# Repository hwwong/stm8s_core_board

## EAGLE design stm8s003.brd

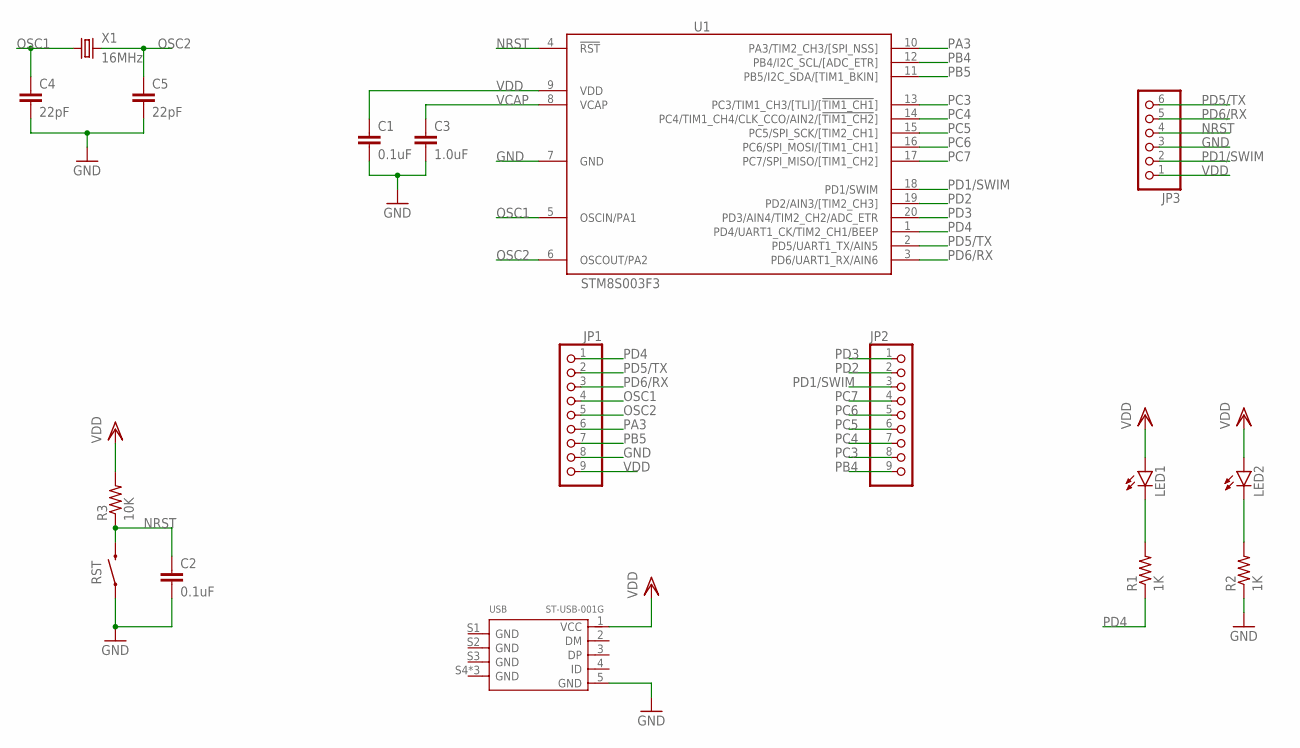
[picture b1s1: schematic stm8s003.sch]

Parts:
C1, C2: 0.1uF; 0603-CAP
C3: 1.0uF; 0603-CAP
C4, C5: 22pF; 0603-CAP
JP1, JP2: PINHD-1X9; 1X09-BIG
JP3: PINHD-1X6; 1X06
LED1, LED2: LED0603; LED-0603
R1, R2: 1K; 0603-RES
R3: 10K; 0603-RES
RST: SWITCH-MOMENTARY-2SMD-1101NE; TACTILE-SWITCH-1101NE
U1: STM8S003F3; TSSOP20
USB: ST-USB-001G; MICRO-USB5+4P-SMD-0.65-B
X1: 16MHz; HC49US

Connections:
GND: C1.2, C2.2, C3.2, C4.2, C5.2, JP1.8, JP3.3, R2.1, RST.1, U1.7 (GND), USB.5 (GND)
unnamed: LED1.C, R1.2
unnamed: LED2.C, R2.2
NRST: C2.1, JP3.4, R3.1, RST.2, U1.4 (!RST)
OSC1: C4.1, JP1.4, U1.5 (OSCIN/PA1), X1.1
OSC2: C5.1, JP1.5, U1.6 (OSCOUT/PA2), X1.2
PA3: JP1.6, U1.10 (PA3/TIM2_CH3/[SPI_NSS])
PB4: JP2.9, U1.12 (PB4/I2C_SCL/[ADC_ETR])
PB5: JP1.7, U1.11 (PB5/I2C_SDA/[TIM1_BKIN])
PC3: JP2.8, U1.13 (PC3/TIM1_CH3/[TLI]/[!TIM1_CH1!])
PC4: JP2.7, U1.14 (PC4/TIM1_CH4/CLK_CCO/AIN2/[!TIM1_CH2!])
PC5: JP2.6, U1.15 (PC5/SPI_SCK/[TIM2_CH1])
PC6: JP2.5, U1.16 (PC6/SPI_MOSI/[TIM1_CH1])
PC7: JP2.4, U1.17 (PC7/SPI_MISO/[TIM1_CH2])
PD1/SWIM: JP2.3, JP3.2, U1.18 (PD1/SWIM)
PD2: JP2.2, U1.19 (PD2/AIN3/[TIM2_CH3])
PD3: JP2.1, U1.20 (PD3/AIN4/TIM2_CH2/ADC_ETR)
PD4: JP1.1, R1.1, U1.1 (PD4/UART1_CK/TIM2_CH1/BEEP)
PD5/TX: JP1.2, JP3.6, U1.2 (PD5/UART1_TX/AIN5)
PD6/RX: JP1.3, JP3.5, U1.3 (PD6/UART1_RX/AIN6)
VCAP: C3.1, U1.8 (VCAP)
VDD: C1.1, JP1.9, JP3.1, LED1.A, LED2.A, R3.2, U1.9 (VDD), USB.1 (VCC)

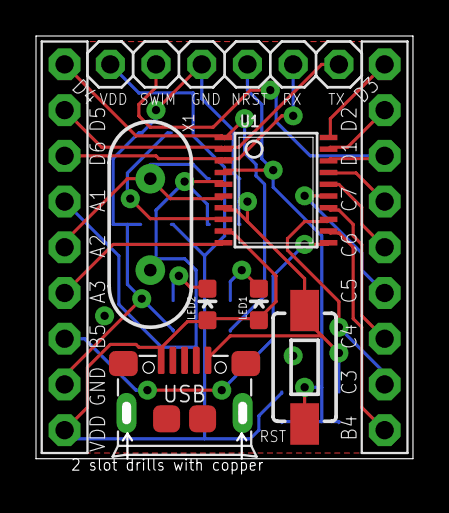
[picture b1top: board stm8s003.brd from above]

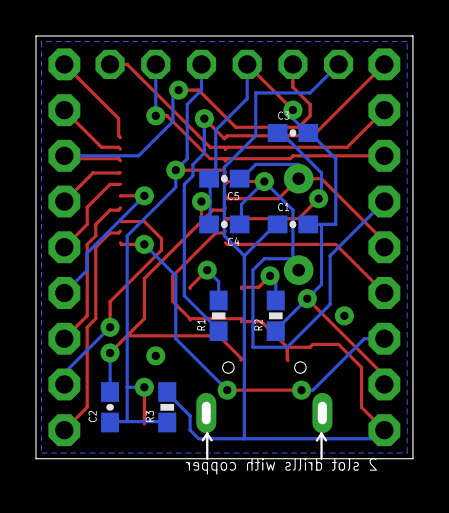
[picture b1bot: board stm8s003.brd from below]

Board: 2 copper layers, 20.9 x 23.5 mm, 17 parts (8 on the bottom side), 22 nets.

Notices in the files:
parts and their libraries:
SparkFun-Capacitors: Licensing: Creative Commons ShareAlike 4.0 International - https://creativecommons.org/licenses/by-sa/4.0
